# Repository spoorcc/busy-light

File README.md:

<div align="center">

# busy-light

**A Wi-Fi status ring for desks, doors and build rooms.**
Sixteen RGB LEDs that show your Jenkins build status or any other level, with no app and no cloud account.

-003399)

[Documentation](docs/README.md) ·
[Requirements](docs/requirements/needs.md) ·
[Architecture decisions](docs/decisions/) ·
[Roadmap](#roadmap) ·
[Contributing](CONTRIBUTING.md) ·
[Security](SECURITY.md)

</div>

---

> **Honest status:** busy-light is in the **design phase**. There is no released firmware, no manufactured
> hardware and no complete approved requirement set yet (22 of 106 requirements are approved). A first prototype board (P1, 46 mm)
> is routed and checked by script, but a review (RV-016) found it **not ready to order**. On 2026-11-28 the owner decided a round
> 58.5 mm successor with 36 LEDs (ADR-0027); its plan passed a readiness review (RV-020) and **no board has been made from it yet**.
> Everything below describes the **intended** product and
> what the project has already proved with desk studies, PC prototypes and CAD experiments.
> Nothing here is certified, and no conformity with any regulation is claimed.

## What is it?

busy-light is a small round device with a ring of 16 individually controllable RGB LEDs. It joins your Wi-Fi,
listens to your build server or fetches its status over REST, and turns that into a colour or a level you can see
from across the room.

The first use case is a **Jenkins build light**: green, red, unstable, running, aborted. The second is a
**level gauge**: the ring fills like a dial from 0 to 100 percent for queue length, test pass rate, or any number
a REST endpoint can give.

The current models have 16 LEDs on a 53 mm housing. The owner decided on 2026-11-28 (ADR-0027, accepted) that the next
prototype has 32 ring LEDs in two arcs plus 4 LEDs under a centre button, on a round 58.5 mm board in a housing of about
65.5 mm. The draft requirements SYS-001 and SYS-028 carry these figures in brackets until the owner approves them.

## Why another status light?

Most status lights need a vendor app, a cloud account or a USB cable to a PC. busy-light is designed around a
different set of goals.

| Goal | What it means |
|------|---------------|
| **Works on a shared, untrusted network** | Per-unit access point password, encrypted provisioning, authenticated and signed updates. |
| **No app, no cloud** | Set-up and configuration through a web page served by the device itself. |
| **Small enough to put anywhere** | About 53 mm across in the current housing model (about 65.5 mm after the decision of 2026-11-28), powered over USB-C. |
| **Cheap to build** | Target assembled board cost of EUR 10 to 20 with a prototype shop. |
| **Source-available and reproducible** | Software, hardware and mechanics are all in this repository, with generated files and checks that anyone can rerun. Code is Apache-2.0. Documentation, hardware and mechanics are free to copy and build for non-commercial use. |
| **Built like a product** | Requirements, decisions, risks and tests are traced from the first line, with EU market access (CE) in mind from day one. |

## Planned features

These are **planned**, taken from the draft requirements in [`docs/requirements/`](docs/requirements/). None is released.

- **RGB LED ring** (16 LEDs in the current models; 32 in two arcs plus 4 under a centre button decided for the next prototype) with status colours, animations and a level (gauge) mode
- **Jenkins first:** receive pushed build events, or poll the Jenkins REST API
- **Mapping without code:** pick a value in the JSON answer, map it to a state or scale it to a level
- **Own access point for set-up:** the device creates a Wi-Fi network with a unique password printed on a label, you open a web page and enter your Wi-Fi details
- **Web interface** served by the device, no app to install
- **WPA2 and WPA2-Enterprise** networks, with user-loadable certificates
- **Over-the-air updates** that are signed and can be checked before they run
- **USB-C power** with safe handling of the available current: a hardware current limit and a firmware limiter on LED brightness
- **Secure boot and flash encryption** (planned for production units)

```mermaid
flowchart LR
    J[Jenkins or other REST source] -- push or poll --> D((busy-light))
    P[Phone or laptop] -- set-up page over the device's own Wi-Fi --> D
    D --> R[LED ring]
    U[USB-C] -- power --> D
```

## What exists today

The project has done a lot of thinking and some experiments, but **no product code or manufactured hardware yet**.

| Area | State |
|------|-------|
| Requirements | Written for needs, system, software, hardware and mechanics (106 entries). **22 are approved by the owner** (all 10 mechanical, 6 hardware including the current-limit gate HW-010 and the shop rules HW-008, 5 software, 1 system); the rest are drafts, among them the amendment texts for the 36-LED board (HW-001, HW-005, SYS-001, SYS-028, SYS-032). |
| Architecture decisions | 27 decision records. **22 are accepted** by the owner (ADR-0011, the housing, only for the prototype; ADR-0023 for its decisions, its text not yet read by the owner), 2 are proposed (ADR-0020 fabrication rules, ADR-0026 the centre-of-ring button) and 3 are superseded (ADR-0009, ADR-0013, ADR-0022). Recent decisions: the gate rework with a stocked hold-off supervisor (ADR-0024, ADR-0025) and the split LED ring on a round 58.5 mm board with the module at the board edge (ADR-0027, 2026-11-28). |
| Risk register | Open. Each risk has a mitigation and a verification link. |
| Reviews | 20 review records ([`docs/reviews/`](docs/reviews/)), from the system design to the built P1 board (RV-016: not ready to order), the gate simplification ADR-0023 (RV-017: rejected as written), the centre-button plan (RV-018), the re-placement plan (RV-019) and the plan for the round 58.5 mm board (RV-020: the readiness pass answered GO for its first two steps, the code for them is not written). |
| Software | Zephyr 4.5.0 workspace pinned. The input-current gate logic (`sw/app/src/gate.c`) has **20 host unit tests that pass** on `native_sim`. The application **builds** for the ESP32-C3 dev kit without warnings, but the gate logic is not in that image yet and **nothing was flashed or run on a board**. A mapping extractor and an LED current limiter were tried as PC-only prototypes (results in the reports, code not in `sw/`). |
| Hardware | A scripted KiCad flow makes the full schematic (USB-C input, CC detection, current-limit gate, hold-off, ESP32-C3 module, 16 LEDs) and the **P1 prototype board**: 46 mm, 4 layers, every assembled part on the top side ([`board-p1/`](hw/kicad/spike-gate/board-p1/README.md)). Script checks pass: strict ERC and DRC with **0 unconnected items** (only the tolerated antenna findings), no via in a pad, supply drops of 7 to 44 mV. The order package (KiKit panel, JLCPCB files) builds, but review RV-016 found the board **not ready to order**: gate-safety gaps after the ADR-0023 simplification, missed placement rules, a main path narrower than 0.6 mm and the housing size limit of MECH-001. The generator and the placement rules now carry the owner's decisions of 2026-11-24 (gate rework ADR-0024, hold-off supervisor TPS3808G01DBVR instead of the unlisted TPS3840 in ADR-0025), but **the stored board predates them and is not regenerated**. The successor is a round 58.5 mm board with 32 ring and 4 centre LEDs (ADR-0027); its plan (plan 08, section S) passed the readiness review for its first two steps (RV-020), and **no placement, routing or check has been run for it**. Part datasheet evidence is recorded in a schema, **none verified**. The surge on the 5 V side is still to be **measured** on a built board. |
| Mechanics | FreeCAD scripts generate the housing (base with USB-C window, button hole, PCB posts and snap hooks, annular back bayonet with lock lips and a mating accessory ring, lid with snap bumps), print coupons for the diffuser and the bayonet, and a tolerance check with tests. **Nothing printed or fit-tested**; the tolerances are assumptions. The fit of the P1 board in the housing is **not checked**. The housing limit is 66 mm (MECH-001, approved amendment of 2026-11-28) and the centre-button requirement MECH-015 is approved, but the generators still make the 53 mm housing and are **not valid for the 58.5 mm board** until the housing plan is revised. |
| Regulatory | Applicability analysis and compliance matrix started; the P1 board changes and the plan for the 36-LED board have a regulatory check (RV-020: photobiological safety of 36 LEDs, antenna at the board edge, EMC of the long data links, thermal are open items). No test evidence collected, no declaration made. |

The reports behind these lines are in [`docs/verification/reports/`](docs/verification/reports/).

### Gallery

All images are generated from text sources or tool exports; none is hand-drawn. None shows a product design: they show the proposal and the experiments.

**Proposed software blocks** (PlantUML source in [`docs/diagrams/plantuml/`](docs/diagrams/plantuml/), draft architecture):

**Prototype board P1, the stored 46 mm board with 16 LEDs (KiCad 10, generated by script, checked by script, not ready to order per RV-016; the round 58.5 mm successor of ADR-0027 has no board yet):**

| Schematic (P1), part 1: USB-C input, CC detection, current-step gate, hold-off, current limit, regulator |
|---|
|  |

| Schematic (P1), part 2: ESP32-C3 module, button, LED buffer, 16 LEDs |
|---|
|  |
| Two crops of one single-sheet schematic, exported with `kicad-cli`; click an image for full size. After ADR-0023 the hold-off output and the current-limit fault share one open-drain line (GATE_OK_RB). Some labels overlap (for example the values of C1 and C27 to C31, and TP6, R16 and R17 at the module) and one note runs past the sheet edge. Not reviewed, not approved. |

| P1 top (3D render) | P1 bottom (3D render) |
|---|---|
|  |  |
| Every assembled part is on the top. Placement by script (seed 47, the best of 16 seeds), routing with Freerouting 2.5.0 and a second router pass that closed the last open connection. | On the bottom: test points TP1 to TP6, the spares C4 and C32 (not fitted, HW-016) and three fiducials. |

| P1 copper layers (seen from the top) | P1 order panel (3D render) |
|---|---|
|  |  |
| In1 is the GND plane; In2 is the +5V plane with 305 mm of signal track (still one piece). 174 vias, none in a pad. Strict DRC: **0 unconnected items**, only the 15 tolerated findings at the ESP32 module (DEV-004). Supply drops (analyst currents): +3V3 7.3, +5V 10.0, VBUS 23.9, VBUS_IC 44.1 mV. | One board per panel with 5 mm rails, four tooling holes, three panel fiducials and four mouse-bite tabs at 105, 217.5, 285 and 330 degrees (KiKit 1.8.1, [`scripts/panel_p1.json`](scripts/panel_p1.json)). Made by [`scripts/fab_p1.sh`](scripts/fab_p1.sh), which also writes the JLCPCB Gerbers, BOM and placement file. |

Regenerate with [`hw/kicad/spike-gate/render_p1_images.sh`](hw/kicad/spike-gate/render_p1_images.sh) (the panel comes from `scripts/fab_p1.sh`). The 3D renders have no component models for most parts and are not a fit check. Not run: housing fit, antenna range, thermal, JLCPCB DFM check and price, bench tests. Details: [`board-p1/README.md`](hw/kicad/spike-gate/board-p1/README.md). The earlier spike board (frozen 2026-11-18) is in [`hw/kicad/spike-gate/board/`](hw/kicad/spike-gate/board/README.md).

| Housing model (FreeCAD script), exploded | Back of the base |
|---|---|
|  |  |
| Generated by [`mech/freecad/housing.py`](mech/freecad/housing.py) and [`accessory.py`](mech/freecad/accessory.py), drawn by [`mech/render_readme_images.sh`](mech/render_readme_images.sh). Parts: lid with snap bumps, base with USB-C window, button hole (working values, the switch is not chosen), posts, snap hooks and the bayonet groove with lock lips, stop and detent; the orange ring is the accessory with three T-lugs. The model passes its own checks (valid solids, no overlap, board fits, the lock holds and stops). **Nothing is printed or fit-tested**; the release tab is not modelled. Results: [`mech-housing-first-model.md`](docs/verification/reports/mech-housing-first-model.md). |

## Roadmap

| Phase | Goal | State |
|-------|------|-------|
| **0. Foundation** | Process, requirements, decisions, risks, regulatory outline, CI | in progress |
| **1. Spikes** | Prove the risky parts on a dev kit: Wi-Fi access point, web page, LED drive, power budget, secure boot | planned, waiting for approval of the spike plan |
| **2. Prototype** | 10 internal prototypes: schematic, board, housing, first firmware | started: P1 board (46 mm) routed and checked by script; RV-016: not ready to order. Next: the round 58.5 mm board with 36 LEDs (plan 08 section S, readiness GO for steps S1 and S2, no code written yet) |
| **3. Verify** | Test cases against approved requirements, pre-compliance tests | planned |
| **4. Release candidate** | Signed firmware, documentation, technical file | planned |

Dates are deliberately not given. Phases start when the previous one has evidence.

## How the project works

busy-light is run like a small regulated company, because the goal is a product that could be sold.

- **Specification before implementation.** No firmware, board or housing change without an approved requirement it traces to.
- **Decisions are recorded.** Costly choices get an architecture decision record with real alternatives, weighted criteria and a critical review.
- **Evidence over claims.** A result is only reported with its test or analysis. What was not run is stated.
- **Everything is code.** Diagrams, hardware (KiCad files generated from scripts) and mechanics (FreeCAD from scripts) are text sources with checks in CI.
- **Documentation is part of the product.** User documentation follows a controlled-language standard (ASD-STE100 principles).
- **EU market access from the start.** Cyber Resilience Act, Radio Equipment Directive, RoHS and friends are tracked in [`docs/regulatory/`](docs/regulatory/README.md). The project states which evidence exists and never states that the product "is compliant".

The full process is in [`docs/process/README.md`](docs/process/README.md).

## Repository layout

| Path | Contents |
|------|----------|
| [`sw/`](sw/) | Zephyr application, west manifest, tests |
| [`hw/`](hw/) | KiCad project, simulation, fabrication outputs, datasheets |
| [`mech/`](mech/) | FreeCAD models, exports, drawings, analysis |
| [`docs/`](docs/README.md) | Process, requirements, architecture, decisions, risk, verification, regulatory, user docs, standards |
| [`scripts/`](scripts/) | Traceability, documentation and CI check scripts |

## Getting started (developers)

**Software** (needs the Zephyr SDK and `west`):

```sh
west init -l sw
west update
west build -b <board> sw/app
```

**Repository checks:**

```sh
python3 -m venv --system-site-packages .venv
.venv/bin/pip install --group dev --group hw
python3 -I scripts/check_traceability.py     # requirements, decisions, risks and tests are linked
python3 -I scripts/check_docs_style.py       # user documentation style
scripts/build_diagrams.sh --check            # diagrams are up to date
.venv/bin/ruff check . && .venv/bin/pytest   # Python tooling
```

**Hardware and mechanical checks** run in CI through `scripts/ci_hw.sh` (KiCad 10) and `scripts/ci_mech.sh` (FreeCAD).
`ci_hw.sh` runs the strict ERC and DRC on the stored boards, and on the P1 board also the no-via-in-pad check and the
power check. `ci_mech.sh` generates the housing models and runs the tolerance check. A check without input reports
**NOT RUN** (for example the regeneration check, which has no generator file yet), so a skipped check is never mistaken
for a pass.

**P1 order package** (needs KiCad 10 with its Python and KiKit 1.8.1 from `scripts/requirements-fab.txt`):

```sh
scripts/fab_p1.sh hw/kicad/spike-gate/board-p1/busy_light_spike.kicad_pcb build/p1-fab   # gates, panel, JLCPCB files
```

## Contributing

Ideas, reviews and critical questions are welcome. Pull requests with code or documents are not accepted until the contributor terms have had a legal check. Please read [`CONTRIBUTING.md`](CONTRIBUTING.md) first.
A good first contribution is to challenge a draft requirement or a proposed decision in
[`docs/decisions/`](docs/decisions/): write down the alternative you would pick and why.

## Security

busy-light is designed for shared networks. To report a vulnerability, follow [`SECURITY.md`](SECURITY.md).
The planned vulnerability handling and key management are drafts under
[`docs/regulatory/technical-file/05-cybersecurity/`](docs/regulatory/technical-file/05-cybersecurity).

## License

| Part | Licence |
|------|---------|
| Code (firmware, scripts, generators, CI, assistant instructions in `.claude/`) | [Apache-2.0](LICENSES/Apache-2.0.txt) |
| Documentation, hardware, mechanics, images | [CC BY-NC-SA 4.0](LICENSES/CC-BY-NC-SA-4.0.txt) |
| Commercial use of the hardware, mechanics or documentation | Separate licence from the owner |

You may copy, study and build from the hardware and mechanical files for non-commercial purposes. Using a unit that you
bought is not restricted. The non-commercial parts are **source-available, not open source hardware**.
Details and the path-by-path map are in [`LICENSE.md`](LICENSE.md) and [`REUSE.toml`](REUSE.toml);
the decision is [ADR-0015](docs/decisions/ADR-0015-licensing-corrections.md). Third-party parts such as Zephyr keep their own licences.
This is not legal advice.

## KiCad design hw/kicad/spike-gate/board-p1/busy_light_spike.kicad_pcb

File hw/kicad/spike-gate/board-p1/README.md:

# P1 board result: one side, 46 mm (plan 08, ADR-0023)

The routed 4-layer P1 board with every assembled part on the top side: batch `p1b8` run 3, completed by the second router pass
of `run_repass.sh` (2026-11-20). Freerouting 2.5.0 is not deterministic across placements and runs, so this is one run, not a
recipe. Script output, never edited by hand. Not reviewed or approved; not "DFx approved", not "fully functional", **not ready
to order** (see Open).

## Images
| Top (3D render) | Bottom (3D render) | Order panel (3D render) |
|---|---|---|
|  |  |  |

Copper layers: [`p1-pcb-layers.png`](../../../../docs/verification/reports/images/p1-pcb-layers.png); schematic:
[`p1-schematic-gate-power.png`](../../../../docs/verification/reports/images/p1-schematic-gate-power.png) and
[`p1-schematic-mcu-leds.png`](../../../../docs/verification/reports/images/p1-schematic-mcu-leds.png). Made on 2026-11-21 by
`render_p1_images.sh board-p1 <package>/panel.kicad_pcb docs/verification/reports/images`, with the panel of a
`scripts/fab_p1.sh` package of this board (input sha256 `cc2457c7...7da6`). The renders have no component models for
most parts and are not a fit check.

## How it was made
- Schematic: `run_full.sh` from the generator after ADR-0023 (97 parts). Regenerated on 2026-11-20 from the source of commit
  `5785f0e`: the schematic is byte-identical to the one the batch used, the netlist equal apart from its date and tool lines.
  Strict ERC 0 findings; 52 of 52 intended nets drawn; two builds identical.
- Placement and first routing (batch p1b8, 2026-11-19): `run_best.sh <netlist> <out> 4` with `P1=1`, `PLACE_GRID=1.0`,
  `PLACE_ANT_KEEPOUT=1`, `PLACE_BLOCKS=3`, `PLACE_ORIENT=1.5`, `KEYFIRST=1`, `PRESTITCH=1`, `FR_THREADS=1`,
  `SPIKE_ALLOW_KNOWN_OPEN=0`, 4 layers, planes `inner`, `SEED_OFFSET` 0. Run 3: placement seeds 33 to 48, seed 47 chosen
  (HPWL 997.9 mm, overlap 0.0 mm2). Spares C4 and C32 on the bottom in 1206, LED capacitors clear of the panel tab sectors.
  After the post-route stitch and the clean-up of `src/pcb_fix.py` one connection stayed open (`/ILIM`, R_ILIM2 pad 2).
  `run_meta.json` describes this router run.
- Second router pass (2026-11-20): `run_repass.sh` on the run folder (`KEYFIRST=1`, `FR_THREADS=1`): every track and via of
  the cleaned board locked, Freerouting 60 passes, then stitch, clean-up and strict DRC again; open connections 1 to 0.
  `repass_meta.json` describes this router run (its `placed_board_sha256` is the sha256 of the input board of the pass). A
  scratch run of the same commands on the same board gave the same router score and the same check results.
- Routing tools: KiCad 10.0.8, Freerouting 2.5.0 (Maven Central jar, sha256 `7f8c6247...a976`), OpenJDK 25.0.5.
- Finishing: `src/pcb_finish.py` in three passes (the third with the silkscreen findings of the first two merged), with the
  fiducials placed before the designators (fix of 2026-11-20). 50 reference designators on the silkscreen, 47 parts without
  room. Fiducials: FID1 on the top, FID4 to FID6 on the bottom; the KiKit panel adds three on the rails (`scripts/panel_p1.json`).
  Routing did not change.
- Sourcing: `src/pcb_sourcing.py` against the schematic: no field changed.

## Checks run on these files (2026-11-20)
- Strict ERC `full`: 0 findings. Strict DRC `stitched-4l` (`SPIKE_ALLOW_KNOWN_OPEN=0`): only the tolerated classes
  `courtyards_overlap` 14 (max 14, all with U9; DEV-004) and `items_not_allowed` 1 (U9 in the hook rule area; DEV-004). No
  unconnected item, no clearance finding. `scripts/ci_hw.sh` exit 0 (its regeneration check is NOT RUN: no
  `hw/kicad/src/generate.py`).
- `src/pcb_fabcheck.py --no-via-in-pad`: PASS. 174 vias, 0 in an SMD pad; track 0.15 mm minimum; via 0.6 / 0.3 mm; annular ring
  0.15 mm on all 174 vias (the absolute minimum, below the recommended ring; ADR-0020 is Proposed).
- `src/pcb_power_check.py` (analyst currents; 50 mV is an analyst target, not a requirement; full-width rule 0.75 x the net's
  width, also the assistant's): +3V3 7.3 mV at 0.5 A, +5V 10.0 mV at 1.0 A, VBUS 23.9 mV at 1.5 A, VBUS_IC 44.1 mV at 1.5 A; every
  case with a full-width path. Planes: In1 GND one piece (13 % removed by other copper), In2 +5V one piece (26 % removed;
  305 mm of signal track on In2).
- Sides: every assembled part on the top. On the bottom: TP1 to TP6, the DNP spares C4 and C32 (out of the BOM), FID4 to FID6.
- `tests/test_board_p1.py`: 6 passed (sides, HW-016 spares within 10 mm of U7 pin 6, HW-017 link, supply drops and full-width
  paths, panel tabs).
- Order package `scripts/fab_p1.sh`: exit 0, all gates passed (strict ERC and DRC, fab check, power check, panel tabs at 105,
  217.5, 285 and 330 deg with the nearest capacitor 4.85 mm from a tab, KiKit panel and JLCPCB files, assembly PDF,
  `fab_check.py`: 88 assembled refs, BOM equals CPL, all on top, ILIM resistors 0.1 %; R22 and U5 without an LCSC number,
  allowed by `scripts/fab_missing_lcsc.txt`). The package is build output and is not committed.

## Open (owner)
- Review RV-016 (2026-11-22, `docs/reviews/RV-016-p1-plan-rev5-as-built-goldfish.md`): **not ready to order**. Gate safety
  after ADR-0023, missed placement rules, a main path below 0.6 mm, the full BOM without C4 and C32, MECH-001 and unverified
  footprints; the board is to be placed and routed again after the owner's decisions (plan 08 section 0.5).
- U5 TPS3840DL40DBVR has no LCSC or JLCPCB listing (the hold-off of HW-010 needs it); R22 candidate up to 20 mohm against
  HW-017 [10] mohm.
- Superseded for the next board: the owner replaced U5 by the TPS3808G01DBVR (ADR-0025, 2026-11-24) and reworked the gate
  (ADR-0024). The generator carries both; this stored board still has the TPS3840 and is not regenerated. The successor is
  the round 58.5 mm board of plan 08 section S (ADR-0027); nothing has been placed or routed for it.
- The assistant's picks: spares on the bottom in 1206; tab azimuths; the 0.75 full-width rule and the 50 mV target.
- Not run: housing fit (FreeCAD), antenna range with the module 5 mm closer to the edge (TC-205), thermal, the fab-release
  workflow on GitHub, JLCPCB DFM upload and price, bench (TC-208, TC-210, TC-216, TC-217).

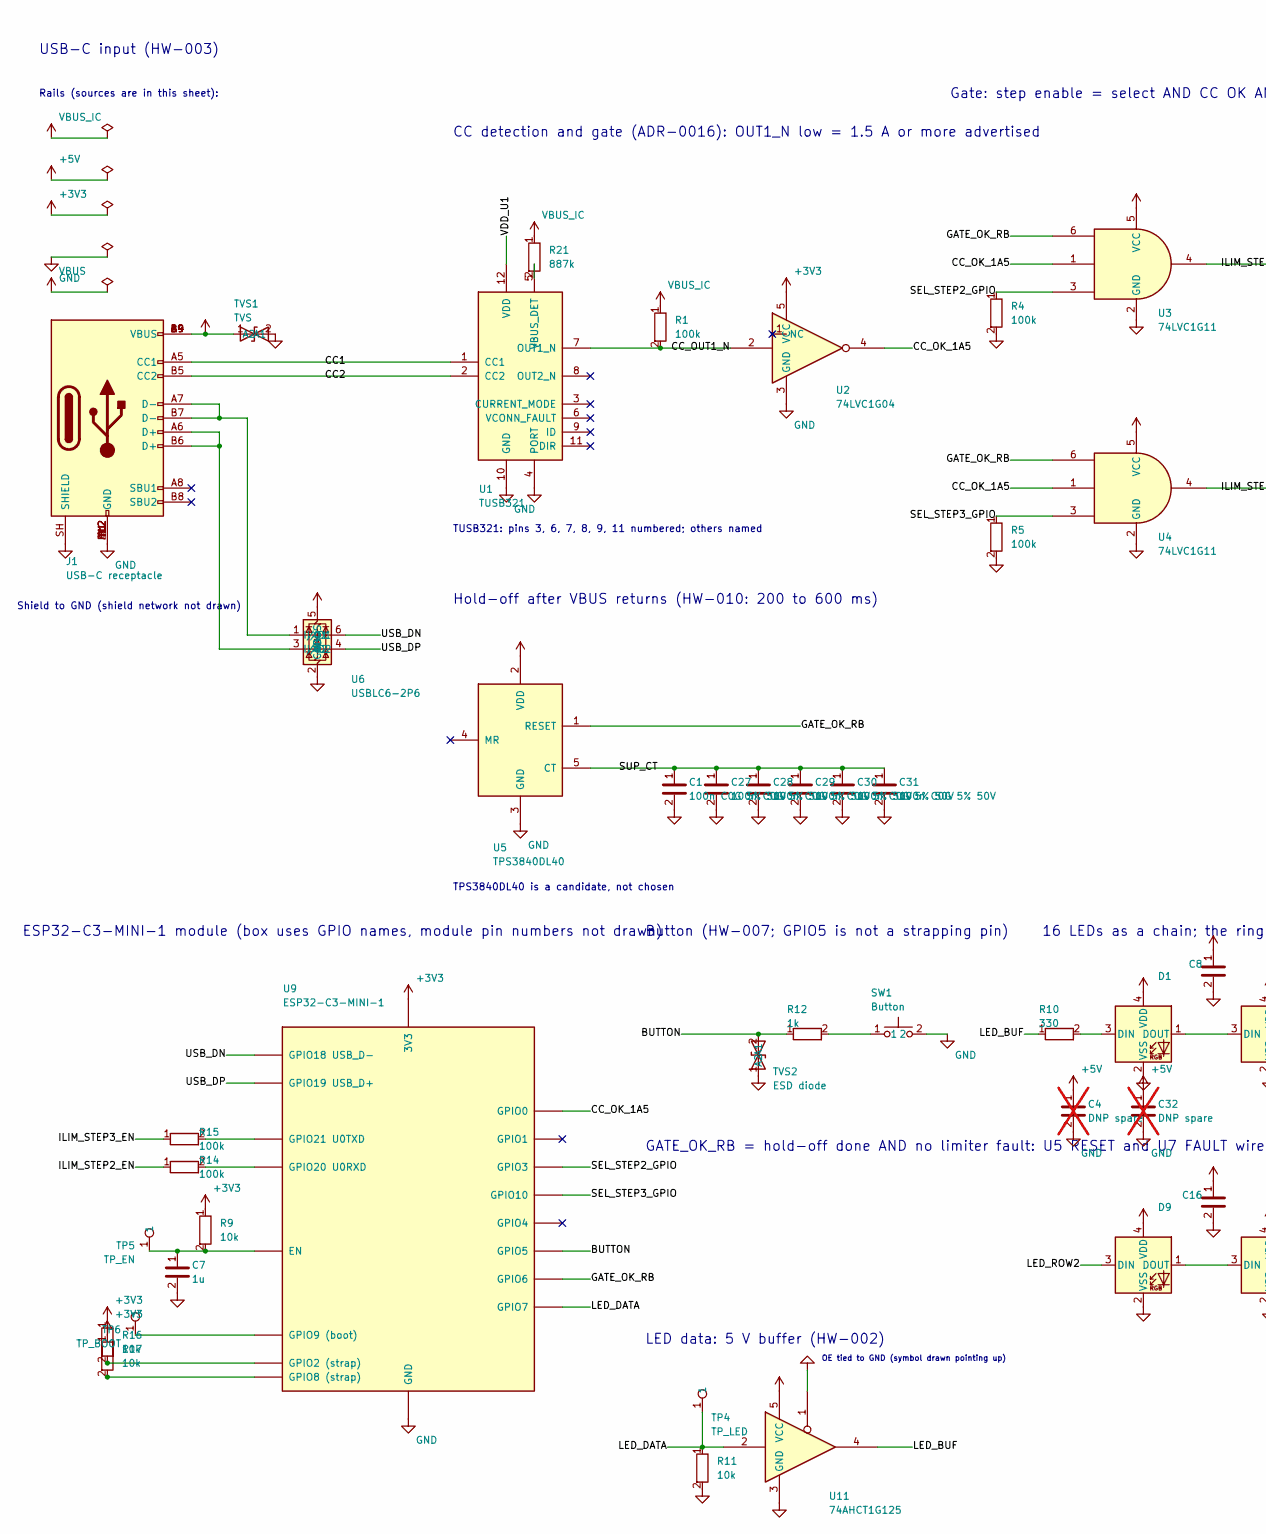
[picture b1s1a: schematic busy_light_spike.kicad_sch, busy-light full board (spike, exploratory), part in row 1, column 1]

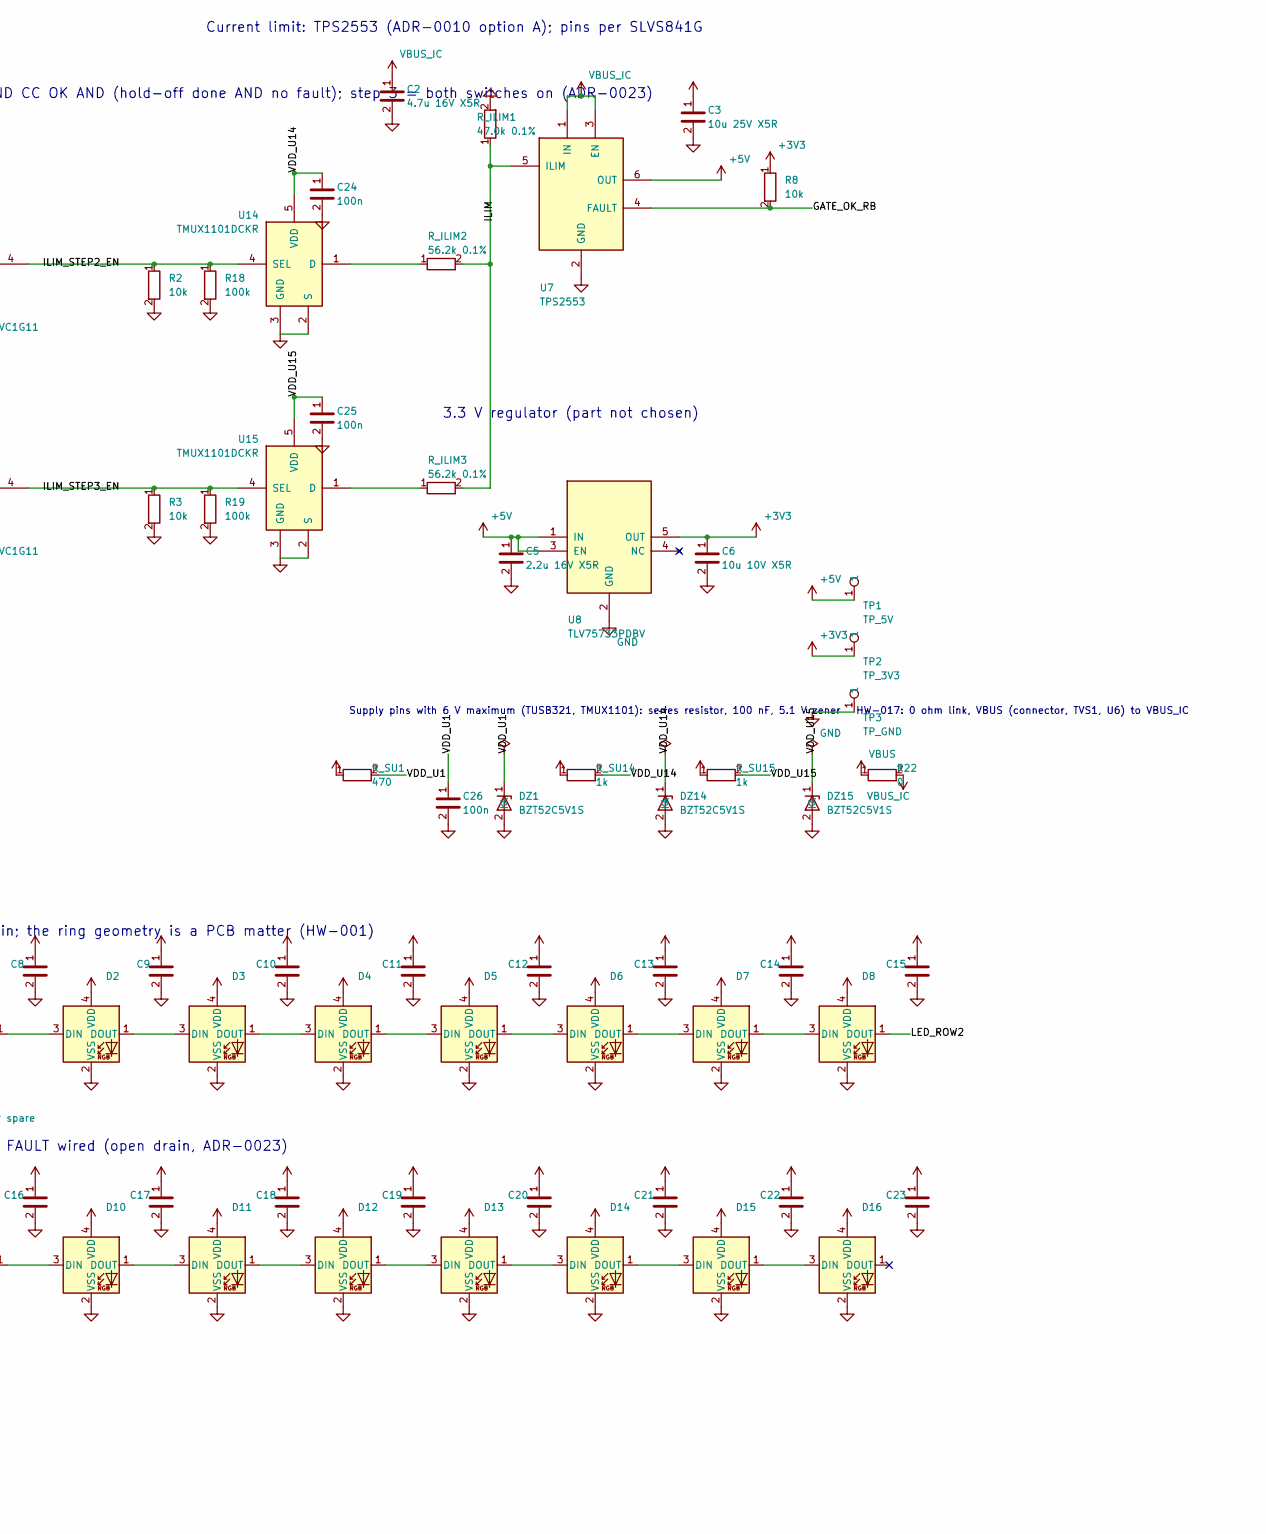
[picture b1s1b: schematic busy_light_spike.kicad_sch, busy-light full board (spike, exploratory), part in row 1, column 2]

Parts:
C1, C27, C28, C29, C30, C31: 100n C0G 5% 50V; C_1206_3216Metric; MPN GRM31C5C1H104JA01L; LCSC C97946
C2: 4.7u 16V X5R; C_0603_1608Metric; MPN CL10A475KO8NNNC; LCSC C19666
C3: 10u 25V X5R; C_0805_2012Metric; MPN CL21A106KAYNNNE; LCSC C15850
C4, C32: DNP spare; C_1206_3216Metric; not fitted
C5: 2.2u 16V X5R; C_0603_1608Metric; MPN CL10A225KO8NNNC; LCSC C23630
C6: 10u 10V X5R; C_0603_1608Metric; MPN CL10A106KP8NNNC; LCSC C19702
C7: 1u; C_0402_1005Metric; MPN CL05A105KA5NQNC; LCSC C52923
C8, C9, C10, C11, C12, C13, C14, C15, C16, C17, C18, C19, C20, C21, C22, C23: 100n; C_0603_1608Metric; MPN CL10B104KB8NNNC; LCSC C1591
C24, C25, C26: 100n; C_0402_1005Metric; MPN CL05B104KO5NNNC; LCSC C1525
D1, D2, D3, D4, D5, D6, D7, D8, D9, D10, D11, D12, D13, D14, D15, D16: WS2812B; LED_WS2812B-2020_PLCC4_2.0x2.0mm; MPN WS2812B-2020; LCSC C965555
DZ1, DZ14, DZ15: BZT52C5V1S; D_SOD-323; MPN BZT52C5V1S; LCSC C545356
J1: USB-C receptacle; USB_C_Receptacle_GCT_USB4085_edge; MPN USB4085-GF-A; LCSC C7095263
R1, R4, R5, R14, R15, R18, R19: 100k; R_0402_1005Metric; MPN 0402WGF1003TCE; LCSC C25741
R2, R3, R8, R9, R11, R16, R17: 10k; R_0402_1005Metric; MPN 0402WGF1002TCE; LCSC C25744
R10: 330; R_0402_1005Metric; MPN 0402WGF3300TCE; LCSC C25104
R12: 1k; R_0402_1005Metric; MPN 0402WGF1001TCE; LCSC C11702
R21: 887k; R_0603_1608Metric; MPN 0603WAF8873T5E; LCSC C23259
R22: 0; R_1206_3216Metric
R_ILIM1: 47.0k 0.1%; R_0603_1608Metric; MPN TD03G4702BT; LCSC C667109
R_ILIM2, R_ILIM3: 56.2k 0.1%; R_0603_1608Metric; MPN TD03G5622BT; LCSC C667119
R_SU1: 470; R_0402_1005Metric; MPN 0402WGF4700TCE; LCSC C25117
R_SU14, R_SU15: 1k; R_0402_1005Metric; MPN 0402WGF1001TCE; LCSC C11702
SW1: Button; SW_SPST_TL3342; MPN TL3342F160QG; LCSC C2886898
TP1: TP_5V; TestPoint_Pad_D1.5mm
TP2: TP_3V3; TestPoint_Pad_D1.5mm
TP3: TP_GND; TestPoint_Pad_D1.5mm
TP4: TP_LED; TestPoint_Pad_D1.5mm
TP5: TP_EN; TestPoint_Pad_D1.5mm
TP6: TP_BOOT; TestPoint_Pad_D1.5mm
TVS1: TVS; D_SOD-323; MPN PESD5V0S1BA,115; LCSC C19224
TVS2: ESD diode; D_SOD-323; MPN PESD3V3L1BA,115; LCSC C51450
U1: TUSB321; X2QFN-12_RWB; MPN TUSB321RWBR; LCSC C139392
U2: 74LVC1G04; Texas_R-PDSO-G5_DCK-5; MPN SN74LVC1G04DCKR; LCSC C8207
U3, U4: 74LVC1G11; SOT-363_SC-70-6; MPN SN74LVC1G11DCKR; LCSC C529281
U5: TPS3840DL40; SOT-23-5; MPN TPS3840DL40DBVR
U6: USBLC6-2P6; SOT-666; MPN USBLC6-2P6; LCSC C15999
U7: TPS2553; SOT-23-6; MPN TPS2553DBVR; LCSC C55266
U8: TLV75733PDBV; SOT-23-5; MPN TLV75733PDBVR; LCSC C485517
U9: ESP32-C3-MINI-1; MPN ESP32-C3-MINI-1-N4; LCSC C2838502
U11: 74AHCT1G125; SOT-353_SC-70-5; MPN SN74AHCT1G125DCKR; LCSC C350557
U14, U15: TMUX1101DCKR; SOT-353_SC-70-5; MPN TMUX1101DCKR; LCSC C2673506

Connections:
+3V3: C6.1, R8.1, R9.1, R16.1, R17.1, TP2.1, U2.5 (VCC), U3.5 (VCC), U4.5 (VCC), U8.5 (OUT), U9.3 (3V3)
+5V: C3.1, C4.1, C5.1, C8.1, C9.1, C10.1, C11.1, C12.1, C13.1, C14.1, C15.1, C16.1, C17.1, C18.1, C19.1, C20.1, C21.1, C22.1, C23.1, C32.1, D1.4 (VDD), D2.4 (VDD), D3.4 (VDD), D4.4 (VDD), D5.4 (VDD), D6.4 (VDD), D7.4 (VDD), D8.4 (VDD), D9.4 (VDD), D10.4 (VDD), D11.4 (VDD), D12.4 (VDD), D13.4 (VDD), D14.4 (VDD), D15.4 (VDD), D16.4 (VDD), TP1.1, U7.6 (OUT), U8.1 (IN), U8.3 (EN), U11.5 (VCC)
/BUTTON: R12.1, TVS2.2 (A2), U9.19 (GPIO5)
/CC1: J1.A5 (CC1), U1.1 (CC1)
/CC2: J1.B5 (CC2), U1.2 (CC2)
/CC_OK_1A5: U2.4, U3.1, U4.1, U9.12 (GPIO0)
/CC_OUT1_N: R1.2, U1.7 (OUT1_N), U2.2
/GATE_OK_RB: R8.2, U3.6, U4.6, U5.1 (RESET), U7.4 (FAULT), U9.20 (GPIO6)
/ILIM: R_ILIM1.1, R_ILIM2.2, R_ILIM3.2, U7.5 (ILIM)
/ILIM_STEP2_EN: R2.1, R14.1, R18.1, U3.4, U14.4 (SEL)
/ILIM_STEP3_EN: R3.1, R15.1, R19.1, U4.4, U15.4 (SEL)
/LED_BUF: R10.1, U11.4
/LED_DATA: R11.1, TP4.1, U9.21 (GPIO7), U11.2
/LED_ROW2: D8.1 (DOUT), D9.3 (DIN)
/SEL_STEP2_GPIO: R4.1, U3.3, U9.6 (GPIO3)
/SEL_STEP3_GPIO: R5.1, U4.3, U9.16 (GPIO10)
/SUP_CT: C1.1, C27.1, C28.1, C29.1, C30.1, C31.1, U5.5 (CT)
/USB_DN: U6.6 (I/O1), U9.26 (GPIO18 USB_D-)
/USB_DP: U6.4 (I/O2), U9.27 (GPIO19 USB_D+)
/VDD_U1: C26.1, DZ1.1 (K), R_SU1.2, U1.12 (VDD)
/VDD_U14: C24.1, DZ14.1 (K), R_SU14.2, U14.5 (VDD)
/VDD_U15: C25.1, DZ15.1 (K), R_SU15.2, U15.5 (VDD)
GND: C1.2, C2.2, C3.2, C4.2, C5.2, C6.2, C7.2, C8.2, C9.2, C10.2, C11.2, C12.2, C13.2, C14.2, C15.2, C16.2, C17.2, C18.2, C19.2, C20.2, C21.2, C22.2, C23.2, C24.2, C25.2, C26.2, C27.2, C28.2, C29.2, C30.2, C31.2, C32.2, D1.2 (VSS), D2.2 (VSS), D3.2 (VSS), D4.2 (VSS), D5.2 (VSS), D6.2 (VSS), D7.2 (VSS), D8.2 (VSS), D9.2 (VSS), D10.2 (VSS), D11.2 (VSS), D12.2 (VSS), D13.2 (VSS), D14.2 (VSS), D15.2 (VSS), D16.2 (VSS), DZ1.2 (A), DZ14.2 (A), DZ15.2 (A), J1.A1 (GND), J1.A12 (GND), J1.B1 (GND), J1.B12 (GND), J1.SH (SHIELD), R2.2, R3.2, R4.2, R5.2, R11.2, R18.2, R19.2, R_ILIM1.2, SW1.2, TP3.1, TVS1.2 (A2), TVS2.1 (A1), U1.4 (PORT), U1.10 (GND), U2.3 (GND), U3.2 (GND), U4.2 (GND), U5.3 (GND), U6.2 (GND), U7.2 (GND), U8.2 (GND), U9.1 (GND), U9.2 (GND), U9.11 (GND), U9.14 (GND), U9.36 (GND), U9.37 (GND), U9.38 (GND), U9.39 (GND), U9.40 (GND), U9.41 (GND), U9.42 (GND), U9.43 (GND), U9.44 (GND), U9.45 (GND), U9.46 (GND), U9.47 (GND), U9.48 (GND), U9.49 (GND), U9.50 (GND), U9.51 (GND), U9.52 (GND), U9.53 (GND), U11.1, U11.3 (GND), U14.2 (S), U14.3 (GND), U15.2 (S), U15.3 (GND)
unnamed: D1.3 (DIN), R10.2
unnamed: D1.1 (DOUT), D2.3 (DIN)
unnamed: D2.1 (DOUT), D3.3 (DIN)
unnamed: D3.1 (DOUT), D4.3 (DIN)
unnamed: D4.1 (DOUT), D5.3 (DIN)
unnamed: D5.1 (DOUT), D6.3 (DIN)
unnamed: D6.1 (DOUT), D7.3 (DIN)
unnamed: D7.1 (DOUT), D8.3 (DIN)
unnamed: D9.1 (DOUT), D10.3 (DIN)
unnamed: D10.1 (DOUT), D11.3 (DIN)
unnamed: D11.1 (DOUT), D12.3 (DIN)
unnamed: D12.1 (DOUT), D13.3 (DIN)
unnamed: D13.1 (DOUT), D14.3 (DIN)
unnamed: D14.1 (DOUT), D15.3 (DIN)
unnamed: D15.1 (DOUT), D16.3 (DIN)
unnamed: J1.A6 (D+), J1.B6 (D+), U6.3 (I/O2)
unnamed: J1.A7 (D-), J1.B7 (D-), U6.1 (I/O1)
unnamed: R12.2, SW1.1
unnamed: R21.2, U1.5 (VBUS_DET)
unnamed: C7.1, R9.2, TP5.1, U9.8 (EN)
unnamed: R16.2, U9.5 (GPIO2 (strap))
unnamed: R17.2, U9.22 (GPIO8 (strap))
unnamed: TP6.1, U9.23 (GPIO9 (boot))
unnamed: R14.2, U9.30 (GPIO20 U0RXD)
unnamed: R15.2, U9.31 (GPIO21 U0TXD)
unnamed: R_ILIM2.1, U14.1 (D)
unnamed: R_ILIM3.1, U15.1 (D)
VBUS: J1.A4 (VBUS), J1.A9 (VBUS), J1.B4 (VBUS), J1.B9 (VBUS), R22.1, TVS1.1 (A1), U6.5 (VBUS)
VBUS_IC: C2.1, R1.1, R21.1, R22.2, R_SU1.1, R_SU14.1, R_SU15.1, U5.2 (VDD), U7.1 (IN), U7.3 (EN)

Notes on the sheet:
USB-C input (HW-003)
CC detection and gate (ADR-0016): OUT1_N low = 1.5 A or more advertised
Gate: step enable = select AND CC OK AND (hold-off done AND no fault); step 3 = both switches on (ADR-0023)
Hold-off after VBUS returns (HW-010: 200 to 600 ms)
Current limit: TPS2553 (ADR-0010 option A); pins per SLVS841G
3.3 V regulator (part not chosen)
TUSB321: pins 3, 6, 7, 8, 9, 11 numbered; others named
TPS3840DL40 is a candidate, not chosen
ESP32-C3-MINI-1 module (box uses GPIO names, module pin numbers not drawn)
Button (HW-007; GPIO5 is not a strapping pin)
GATE_OK_RB = hold-off done AND no limiter fault: U5 RESET and U7 FAULT wired (open drain, ADR-0023)
OE tied to GND (symbol drawn pointing up)
LED data: 5 V buffer (HW-002)
16 LEDs as a chain; the ring geometry is a PCB matter (HW-001)
Rails (sources are in this sheet):
Shield to GND (shield network not drawn)
Supply pins with 6 V maximum (TUSB321, TMUX1101): series resistor, 100 nF, 5.1 V zener
HW-017: 0 ohm link, VBUS (connector, TVS1, U6) to VBUS_IC

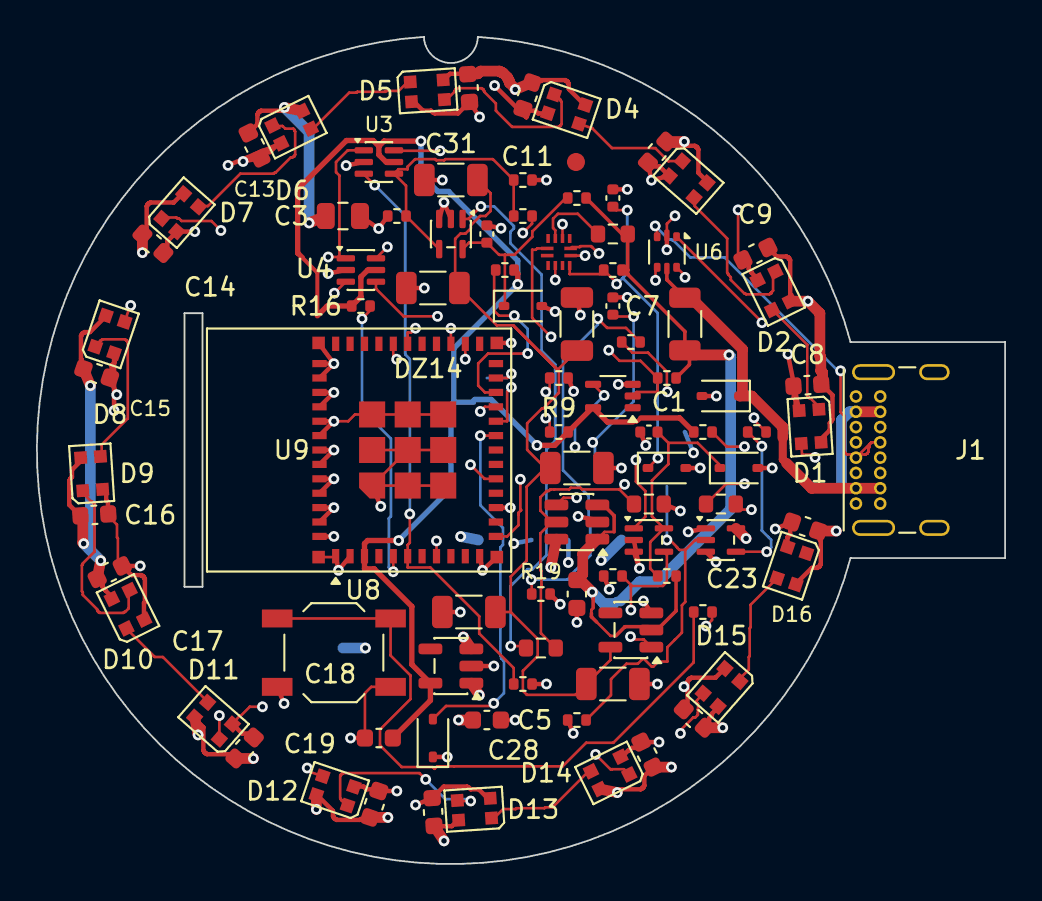
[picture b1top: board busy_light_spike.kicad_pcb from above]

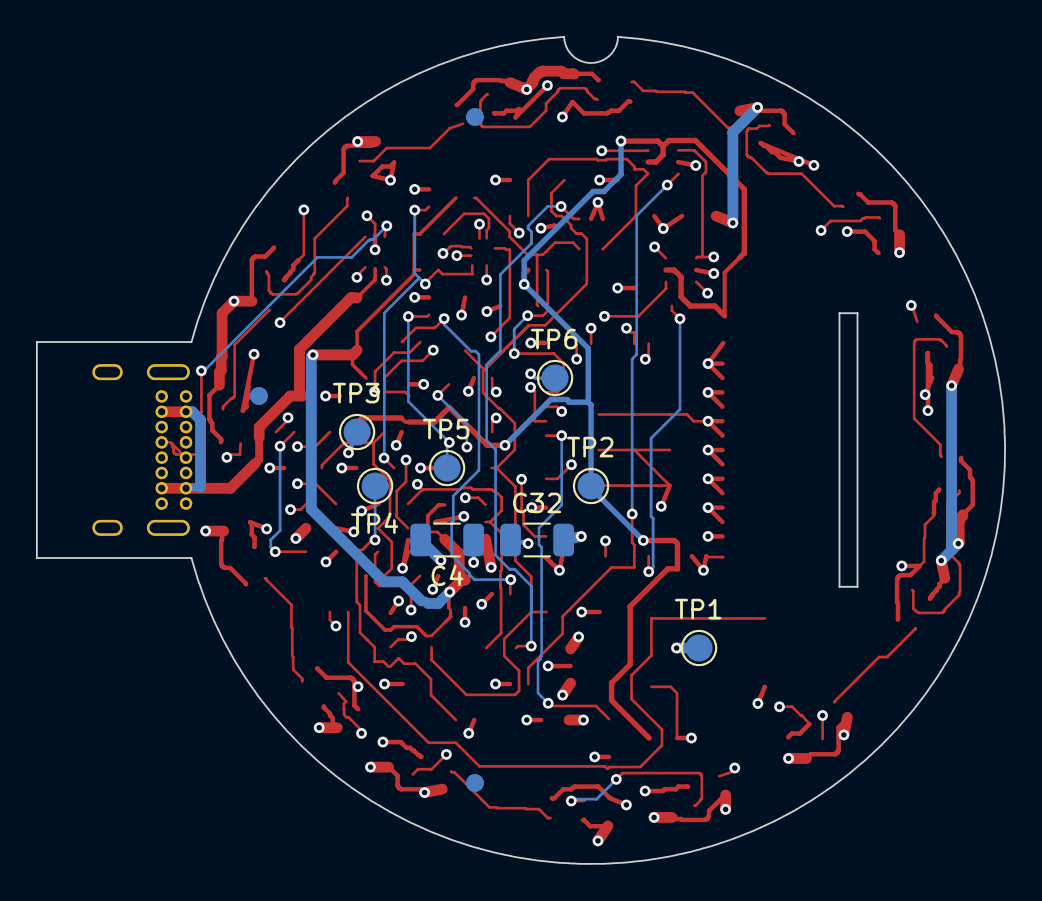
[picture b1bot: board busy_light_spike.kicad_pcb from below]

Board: 4 copper layers, 53.8 x 45.9 mm, 101 parts (11 on the bottom side), 52 nets.

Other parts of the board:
FID1, FID4, FID5, FID6: Fiducial

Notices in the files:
README.md:
Docs, hardware, mechanics: CC BY-NC-SA 4.0
